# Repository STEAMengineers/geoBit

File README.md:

# geoBit
A GPS device for route tracking, GPS art or logging for OSM

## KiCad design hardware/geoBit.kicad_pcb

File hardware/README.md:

# Hardware

### Controller
[RP2354a](https://www.lcsc.com/product-detail/C41378174.html)

### Battery charger
[Injoinic IP5306-I2C](https://www.lcsc.com/product-detail/C488349.html)
Provides 2.1A boosted output at 5V. Use I2C to set registers to prevent the chip from entering sleep mode and read battery charge status. 

[Details of register settings](https://github.com/AvinasheeTech/IP5306_I2C)

### SD card
Uses SDIO (Four line) interface. The interface is protected with an [ST EMIF06-MSD02N16](https://www.lcsc.com/product-detail/C5267594.html?s_z=n_C5267594) chip

### GPS
[ATGM336H-6N-74](https://www.lcsc.com/product-detail/C5804601.html)

### Screen
[Good display GDEY0154D67](https://www.good-display.com/product/388.html)

### GPIO

| Pin  | Name  | Function  | Notes |
|---|---|---|---|
| GPIO_0  | CHGR_SDA  | 	I2C0 SDA  | |
| GPIO_1 | CHGR_SCL  | 	I2C0 SCL  | |
| GPIO_2 | CHGR_IRQ  | 	SIO  | |
| GPIO_3 | BUTTON1  | 	SIO  | |
| GPIO_4 | BUTTON2 | 	SIO  | |
| GPIO_5 | FILTERED_SD_CLK  | 	SIO  | |
| GPIO_6 | FILTERED_SD_CMD  | 	SIO  | |
| GPIO_7 | FILTERED_SD_DAT0  | 	SIO  | |
| GPIO_8 | FILTERED_SD_DAT1  | 	SIO  | |
| GPIO_9 | FILTERED_SD_DAT2  | 	SIO  | |
| GPIO_10 | FILTERED_SD_DAT3  | 	SIO  | |
| GPIO_11 | FILTERED_SD_DET  | 	SIO  | |
| GPIO_12 | GPS_RX  | 	UART0_TX  | |
| GPIO_13 | GPS_TX  | 	UART0_RX  | |
| GPIO_14 | GPS_1PPS  | 	SIO  | |
| GPIO_15 | STATUS_LED  | 	SIO  | |
| GPIO_16 | BUTTON3  | 	SIO  | |
| GPIO_17 | EINK_CS  | 	SPI1_CSn  | |
| GPIO_18 | EINK_SCLK  | 	SPI1_SCK  | |
| GPIO_19 | EINK_SDI  | 	SPI1_TX  | |
| GPIO_20 | EINK_D/C  | 	SIO  | |
| GPIO_21 | EINK_RES  | 	SIO  | |
| GPIO_22 | EINK_BUSY  | 	SIO  | |
| GPIO_23 | UNALLOCATED  | 	SIO  | |
| GPIO_24 | UNALLOCATED  | 	SIO  | |
| GPIO_25 | UNALLOCATED  | 	SIO  | |
| GPIO_26 | UNALLOCATED  | 	SIO  | ADC |
| GPIO_27 | UNALLOCATED  | 	SIO  | ADC |
| GPIO_28 | UNALLOCATED  | 	SIO  | ADC |
| GPIO_29 | UNALLOCATED  | 	SIO  | ADC |

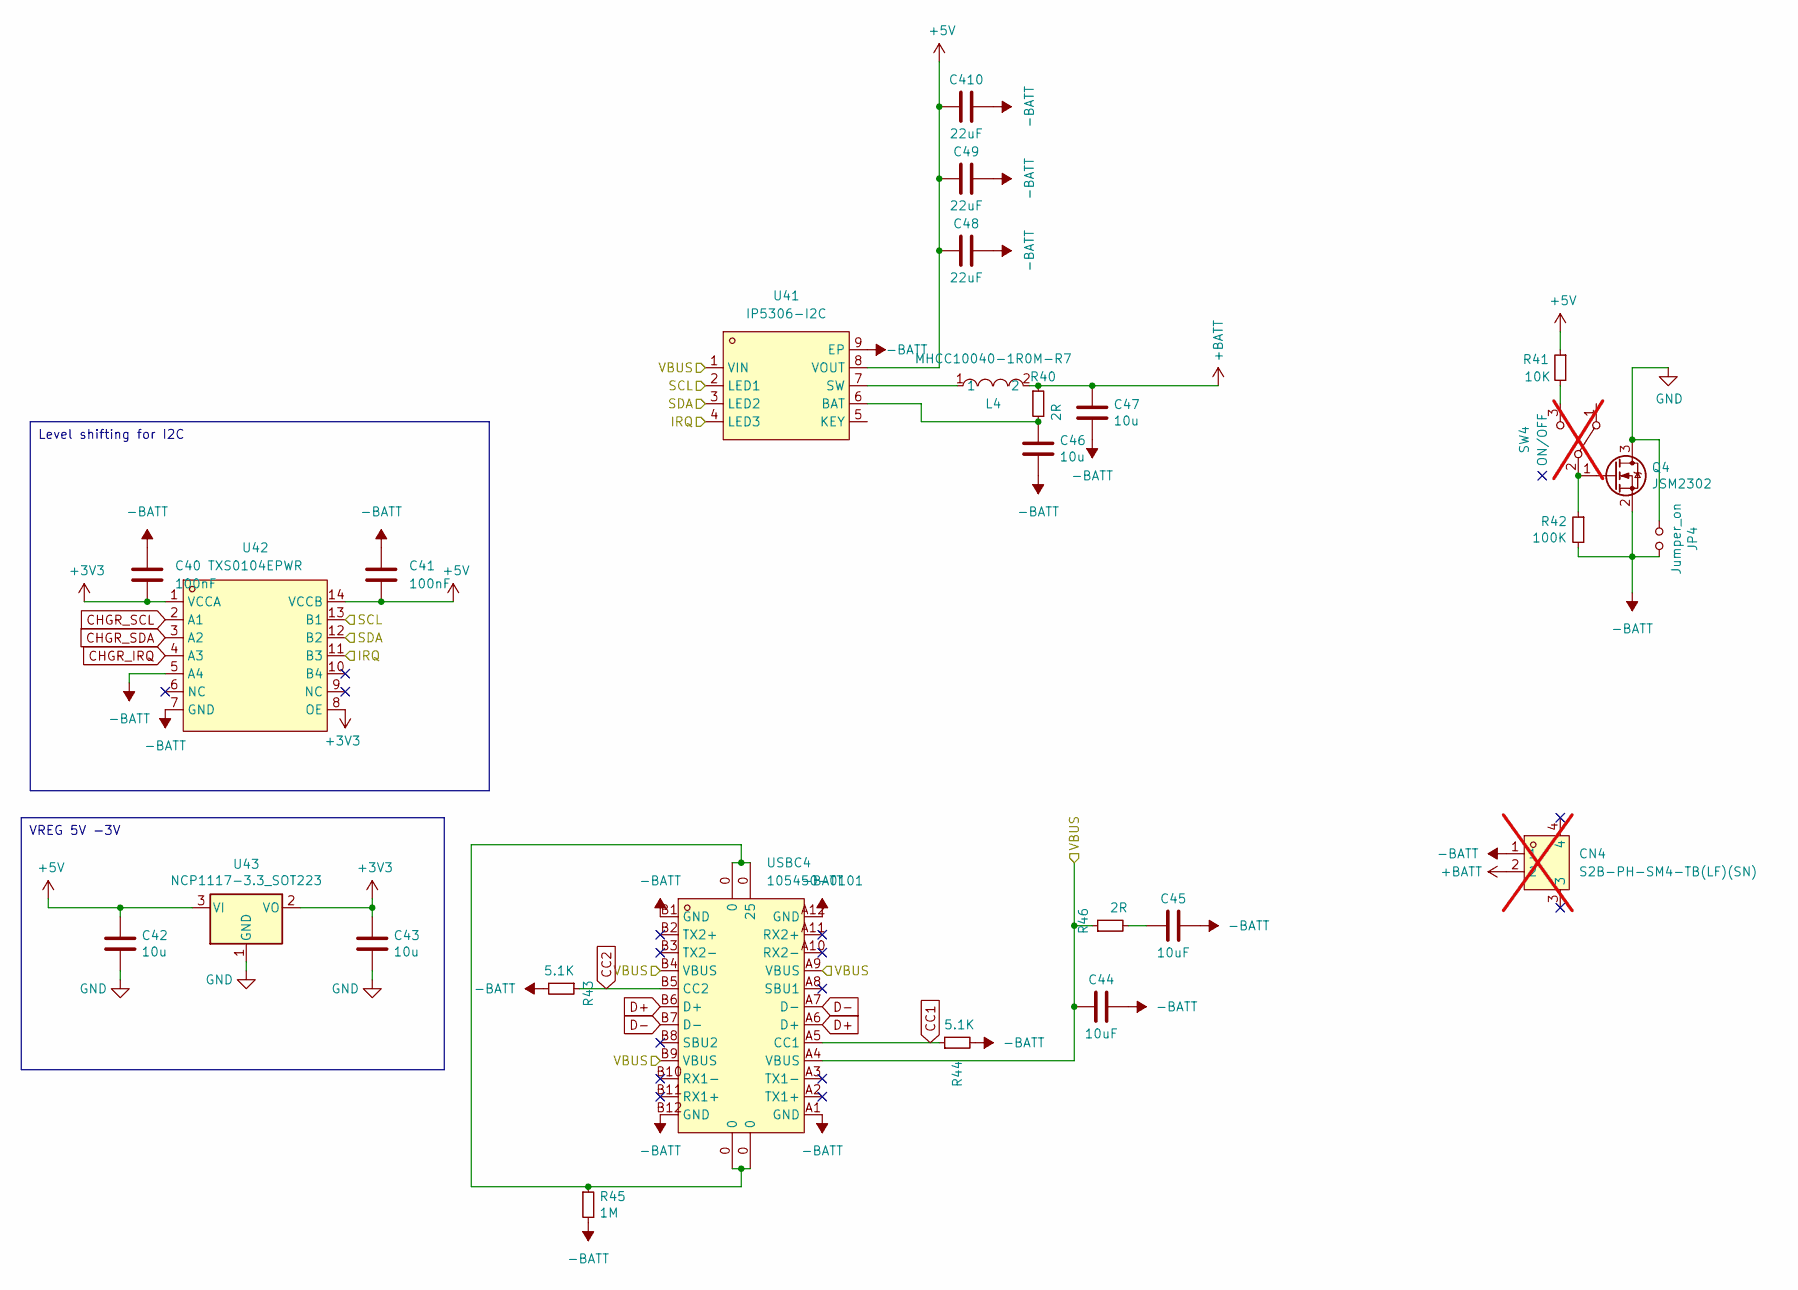
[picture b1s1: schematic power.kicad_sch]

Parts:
C40, C41: 100nF; C_0402_1005Metric_Pad0.74x0.62mm_HandSolder; LCSC C1525
C42, C43, C46, C47: 10u; C_0805_2012Metric
C44, C45: 10uF; C_0603_1608Metric_Pad1.08x0.95mm_HandSolder; LCSC C76614
C48, C49, C410: 22uF; C_0402_1005Metric_Pad0.74x0.62mm_HandSolder; LCSC C2179118
CN4: S2B-PH-SM4-TB(LF)(SN); CONN-SMD_P2.00_S2B-PH-SM4-TB-LF-SN; LCSC Part C295747; not fitted
JP4: Jumper_on; SolderJumper-2_P1.3mm_Open_RoundedPad1.0x1.5mm
L4: MHCC10040-1R0M-R7; IND-SMD_L11.6-W10.1; LCSC Part C280565
Q4: JSM2302; SOT-23; LCSC C916403
R40, R46: 2R; R_0402_1005Metric; Farnell 2447404
R41: 10K; R_0402_1005Metric; Farnell 2331740
R42: 100K; R_0402_1005Metric; Farnell 2073355
R43, R44: 5.1K; R_0402_1005Metric_Pad0.72x0.64mm_HandSolder; Farnell 2447404
R45: 1M; R_0402_1005Metric_Pad0.72x0.64mm_HandSolder; LCSC C26083
SW4: ON/OFF; SW_Slide_SPDT_Angled_CK_OS102011MA1Q; Farnell 1201431; not fitted
U41: IP5306-I2C; ESOP-8_L4.9-W3.9-P1.27-LS6.0-BL-EP2.0; LCSC Part C488349
U42: TXS0104EPWR; TSSOP-14_L5.0-W4.4-P0.65-LS6.4-BL; LCSC Part C44955
U43: NCP1117-3.3_SOT223; SOT-223-3_TabPin2; LCSC C26537
USBC4: 105450-0101; USB-C-SMD_TYPE-C-USB-18; LCSC C134092

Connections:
+3V3: C40.2, C43.1, U42.1 (VCCA), U42.8 (OE), U43.2 (VO); also elsewhere on the board
+5V: C41.2, C42.1, C48.1, C49.1, C410.1, R41.1, U41.8 (VOUT), U42.14 (VCCB), U43.3 (VI)
+BATT: C47.1, CN4.2, L4.2, R40.1
-BATT: C40.1, C41.1, C44.2, C45.2, C46.2, C47.2, C48.2, C49.2, C410.2, CN4.1, JP4.1, Q4.2 (S), R42.2, R43.2, R44.2, R45.2, U41.9 (EP), U42.5 (A4), U42.7 (GND), USBC4.A1 (GND), USBC4.A12 (GND), USBC4.B1 (GND), USBC4.B12 (GND); also elsewhere on the board
/power/IRQ: U41.4 (LED3), U42.11 (B3)
/power/SCL: U41.2 (LED1), U42.13 (B1)
/power/SDA: U41.3 (LED2), U42.12 (B2)
/power/VBUS: C44.1, R46.1, U41.1 (VIN), USBC4.A4 (VBUS), USBC4.A9 (VBUS), USBC4.B4 (VBUS), USBC4.B9 (VBUS); also elsewhere on the board
CHGR_IRQ: U42.4 (A3); also elsewhere on the board
CHGR_SCL: U42.2 (A1); also elsewhere on the board
CHGR_SDA: U42.3 (A2); also elsewhere on the board
GND: C42.2, C43.2, JP4.2, Q4.3 (D), U43.1 (GND); also elsewhere on the board
unnamed: C45.1, R46.2
unnamed: Q4.1 (G), R42.1, SW4.2 (B)
unnamed: R45.1, USBC4.0
unnamed: R41.2, SW4.3 (C)
unnamed: C46.1, R40.2, U41.6 (BAT)
unnamed: L4.1, U41.7 (SW)
unnamed 73: R44.1, USBC4.A5 (CC1); also elsewhere on the board
unnamed 74: R43.1, USBC4.B5 (CC2); also elsewhere on the board
unnamed: USBC4.A6 (D+), USBC4.B6 (D+)
unnamed: USBC4.A7 (D-), USBC4.B7 (D-)

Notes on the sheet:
Level shifting for I2C
VREG 5V -3V

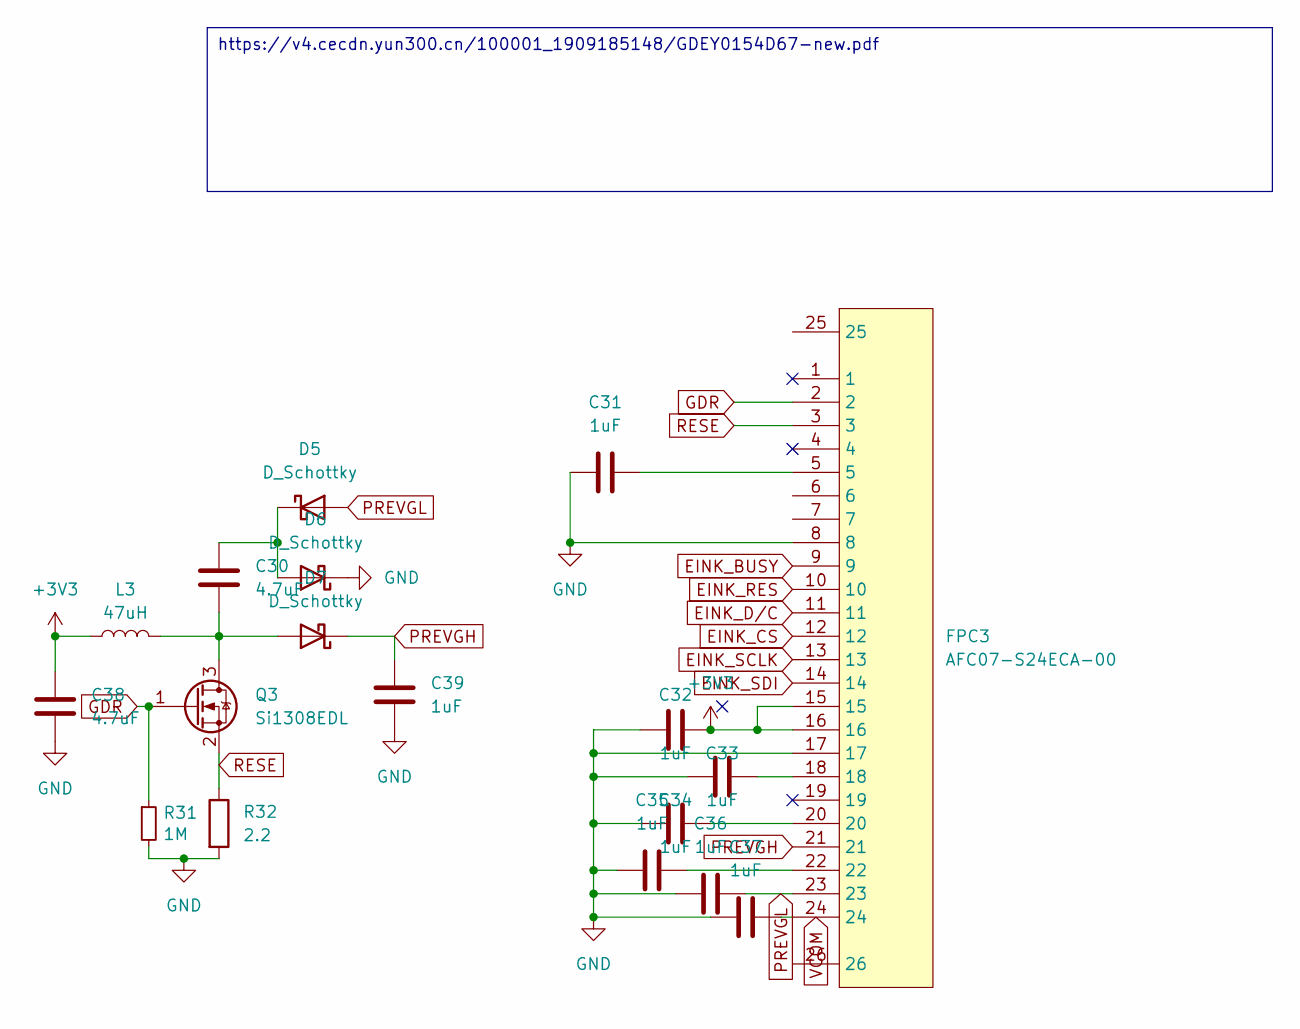
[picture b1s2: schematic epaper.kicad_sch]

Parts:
C30, C38: 4.7uF; C_0402_1005Metric; lcsc C6119795
C31, C32, C33, C34, C35, C36, C37, C39: 1uF; C_0402_1005Metric; lcsc C52923
D5, D6, D7: D_Schottky; D_SOD-323; lcsc C21714236
FPC3: AFC07-S24ECA-00; FPC-SMD_AFC07-S24ECA-00; LCSC Part C262643
L3: 47uH; L_0805_2012Metric; lcsc C19188767
Q3: Si1308EDL; SOT-323_SC-70; lcsc C7603347
R31: 1M; R_0402_1005Metric; LCSC C26083
R32: 2.2; R_0402_1005Metric; lcsc C327251

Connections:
+3V3: C32.1, C38.1, FPC3.15, FPC3.16, L3.1; also elsewhere on the board
EINK_BUSY: FPC3.9; also elsewhere on the board
EINK_CS: FPC3.12; also elsewhere on the board
EINK_D/C: FPC3.11; also elsewhere on the board
EINK_RES: FPC3.10; also elsewhere on the board
EINK_SCLK: FPC3.13; also elsewhere on the board
EINK_SDI: FPC3.14; also elsewhere on the board
GDR: FPC3.2, Q3.1 (G), R31.1
GND: C31.2, C32.2, C33.2, C34.2, C35.2, C36.2, C37.2, C38.2, C39.1, D6.1 (K), FPC3.8, FPC3.17, R31.2, R32.2; also elsewhere on the board
unnamed: C31.1, FPC3.5
unnamed: C33.1, FPC3.18
unnamed: C34.1, FPC3.20
unnamed: C35.1, FPC3.22
unnamed: C37.1, FPC3.24
unnamed: C30.1, D5.1 (K), D6.2 (A)
unnamed: C30.2, D7.2 (A), L3.2, Q3.3 (D)
PREVGH: C39.2, D7.1 (K), FPC3.21
PREVGL: C36.1, D5.2 (A), FPC3.23
RESE: FPC3.3, Q3.2 (S), R32.1

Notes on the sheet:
https://v4.cecdn.yun300.cn/100001_1909185148/GDEY0154D67-new.pdf

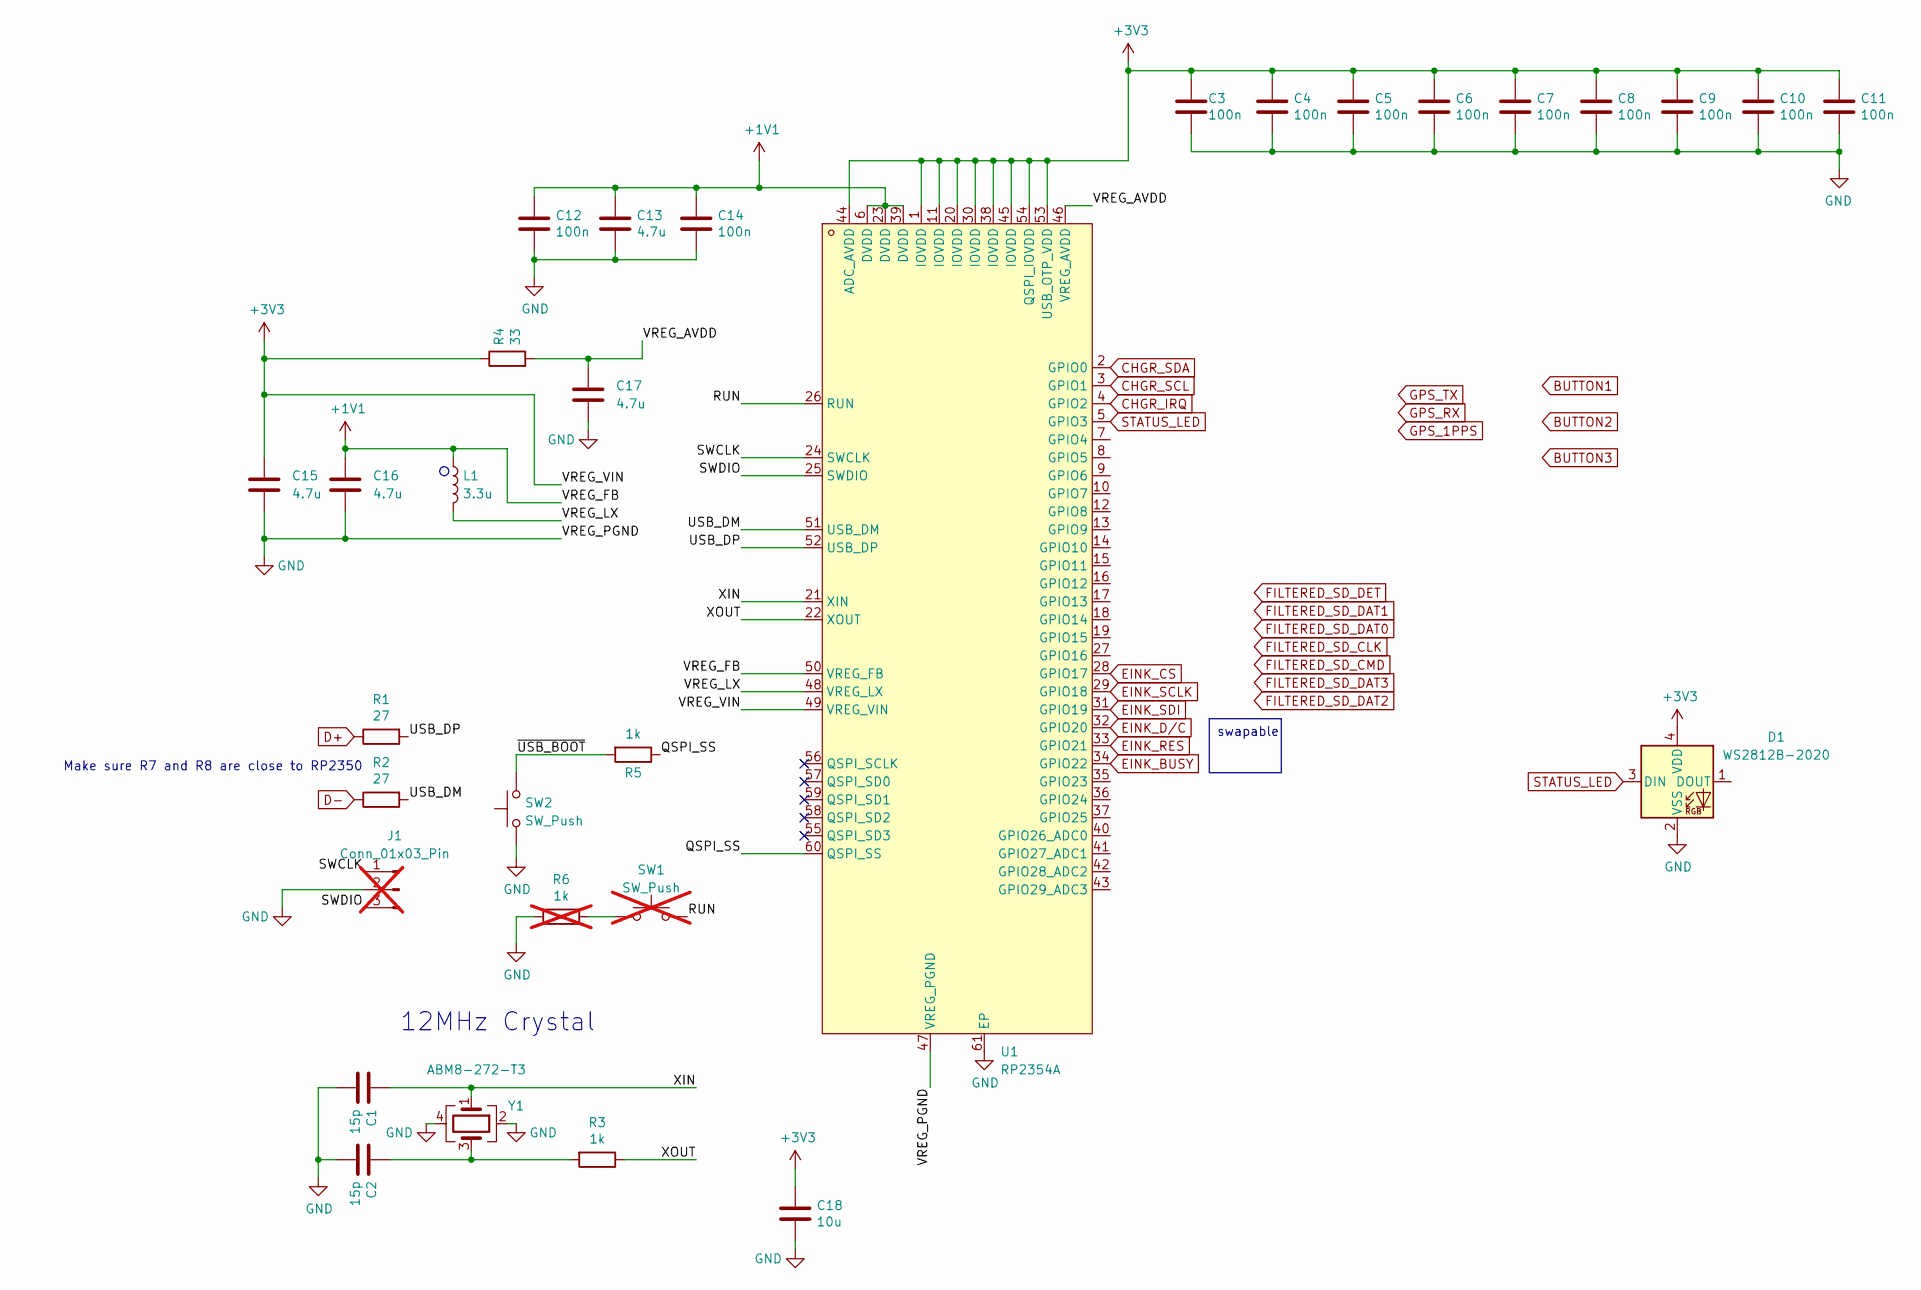
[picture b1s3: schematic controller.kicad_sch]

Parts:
C1, C2: 15p; C_0402_1005Metric; LCSC C326803
C3, C4, C5, C6, C7, C8, C9, C10, C11, C12, C14: 100n; C_0402_1005Metric; LCSC C77020
C13: 4.7u; C_0402_1005Metric
C15, C16: 4.7u; C_0603_1608Metric; LCSC C1705
C17: 4.7u; C_0402_1005Metric; LCSC C23733
C18: 10u; C_0805_2012Metric
D1: WS2812B-2020; LED_WS2812B-2020_PLCC4_2.0x2.0mm
J1: Conn_01x03_Pin; PinHeader_1x03_P2.54mm_Vertical; not fitted
L1: 3.3u; IND-SMD_L2.0-W1.6_AOTA-B201610S3R3-101-T; LCSC C42411119
R1, R2: 27; R_0402_1005Metric; LCSC C138021
R3, R5: 1k; R_0402_1005Metric; LCSC C106235
R4: 33; R_0402_1005Metric; LCSC C138002
R6: 1k; R_0402_1005Metric; LCSC C106235; not fitted
SW1: SW_Push; SW-SMD_L3.9-W3.0-P4.45; LCSC C720477; not fitted
SW2: SW_Push; SW-SMD_L3.9-W3.0-P4.45; LCSC C720477
U1: RP2354A; QFN-60_L7.0-W7.0-P0.40-TL-EP3.4; LCSC Part C41378174
Y1: ABM8-272-T3; Crystal_SMD_3225-4Pin_3.2x2.5mm; LCSC C20625731

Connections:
+1V1: C12.1, C13.1, C14.1, C16.1, L1.1, U1.6 (DVDD), U1.23 (DVDD), U1.39 (DVDD), U1.50 (VREG_FB)
+3V3: C3.1, C4.1, C5.1, C6.1, C7.1, C8.1, C9.1, C10.1, C11.1, C15.1, C18.1, D1.4 (VDD), J1.5, R4.1, U1.1 (IOVDD), U1.11 (IOVDD), U1.20 (IOVDD), U1.30 (IOVDD), U1.38 (IOVDD), U1.44 (ADC_AVDD), U1.45 (IOVDD), U1.49 (VREG_VIN), U1.53 (USB_OTP_VDD), U1.54 (QSPI_IOVDD); also elsewhere on the board
/controller/QSPI_SS: R5.1, U1.60 (QSPI_SS)
/controller/RUN: SW1.2, U1.26 (RUN)
/controller/SWCLK: J1.1, U1.24 (SWCLK)
/controller/SWDIO: J1.3, U1.25 (SWDIO)
/controller/USB_DM: R2.2, U1.51 (USB_DM)
/controller/USB_DP: R1.2, U1.52 (USB_DP)
/controller/VREG_AVDD: C17.1, R4.2, U1.46 (VREG_AVDD)
/controller/VREG_LX: L1.2, U1.48 (VREG_LX)
/controller/XIN: C1.1, U1.21 (XIN), Y1.1
/controller/XOUT: R3.1, U1.22 (XOUT)
/controller/~USB_BOOT: R5.2, SW2.2
BUTTON2: U1.7 (GPIO4); also elsewhere on the board
BUTTON3: U1.27 (GPIO16); also elsewhere on the board
CHGR_IRQ: U1.4 (GPIO2); also elsewhere on the board
CHGR_SCL: U1.3 (GPIO1); also elsewhere on the board
CHGR_SDA: U1.2 (GPIO0); also elsewhere on the board
D+: R1.1; also elsewhere on the board
D-: R2.1; also elsewhere on the board
EINK_BUSY: U1.34 (GPIO22); also elsewhere on the board
EINK_CS: U1.28 (GPIO17); also elsewhere on the board
EINK_D/C: U1.32 (GPIO20); also elsewhere on the board
EINK_RES: U1.33 (GPIO21); also elsewhere on the board
EINK_SCLK: U1.29 (GPIO18); also elsewhere on the board
EINK_SDI: U1.31 (GPIO19); also elsewhere on the board
FILTERED_SD_CLK: U1.8 (GPIO5); also elsewhere on the board
FILTERED_SD_CMD: U1.9 (GPIO6); also elsewhere on the board
FILTERED_SD_DAT0: U1.10 (GPIO7); also elsewhere on the board
FILTERED_SD_DAT1: U1.12 (GPIO8); also elsewhere on the board
FILTERED_SD_DAT2: U1.13 (GPIO9); also elsewhere on the board
FILTERED_SD_DAT3: U1.14 (GPIO10); also elsewhere on the board
GND: C1.2, C2.2, C3.2, C4.2, C5.2, C6.2, C7.2, C8.2, C9.2, C10.2, C11.2, C12.2, C13.2, C14.2, C15.2, C16.2, C17.2, C18.2, D1.2 (VSS), J1.2, J1.4, R6.2, SW2.1, U1.47 (VREG_PGND), U1.61 (EP), Y1.2, Y1.4; also elsewhere on the board
GPIO23: J1.6, U1.35 (GPIO23)
GPIO24: J1.7, U1.36 (GPIO24)
GPIO25: J1.8, U1.37 (GPIO25)
GPIO26_ADC0: J1.9, U1.40 (GPIO26_ADC0)
GPIO27_ADC1: J1.10, U1.41 (GPIO27_ADC1)
GPIO28_ADC2: J1.11, U1.42 (GPIO28_ADC2)
GPIO29_ADC3: J1.12, U1.43 (GPIO29_ADC3)
GPS_1PPS: U1.18 (GPIO14); also elsewhere on the board
GPS_RX: U1.16 (GPIO12); also elsewhere on the board
GPS_TX: U1.17 (GPIO13); also elsewhere on the board
unnamed: C2.1, R3.2, Y1.3
unnamed: R6.1, SW1.1
SD_DET: U1.15 (GPIO11); also elsewhere on the board

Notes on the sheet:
swapable
Make sure R7 and R8 are close to RP2350
12MHz Crystal

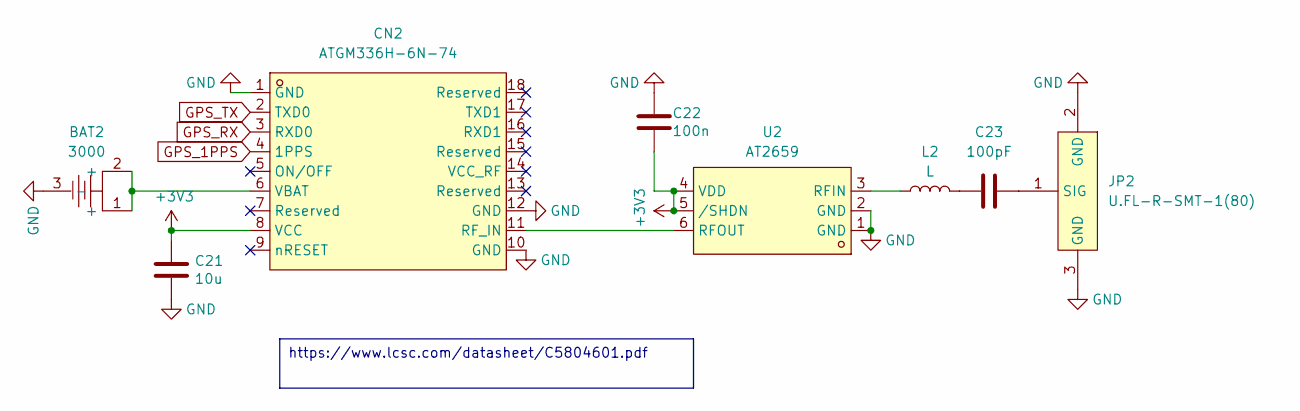
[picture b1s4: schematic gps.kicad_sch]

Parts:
BAT2: 3000; BAT-SMD_CR1202; LCSC Part C238097
C21: 10u; C_0805_2012Metric
C22: 100n; C_0402_1005Metric; LCSC C77020
C23: 100pF; C_0402_1005Metric_Pad0.74x0.62mm_HandSolder; lcsc C106200
CN2: ATGM336H-6N-74; ATGM336H-5N31; LCSC Part C5804601
JP2: U.FL-R-SMT-1(80); RF-SMD_FRF05002-JSS103M; LCSC Part C88374
L2: L; L_0402_1005Metric; lcsc C77110
U2: AT2659; DFN-6_L1.6-W1.0-P0.55-BL; LCSC Part C92450

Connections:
+3V3: C21.1, C22.2, CN2.8 (VCC), U2.4 (VDD), U2.5 (/SHDN); also elsewhere on the board
GND: BAT2.3 (-), C21.2, C22.1, CN2.1 (GND), CN2.10 (GND), CN2.12 (GND), JP2.2 (GND), JP2.3 (GND), U2.1 (GND), U2.2 (GND); also elsewhere on the board
GPS_1PPS: CN2.4 (1PPS); also elsewhere on the board
GPS_RX: CN2.3 (RXD0); also elsewhere on the board
GPS_TX: CN2.2 (TXD0); also elsewhere on the board
unnamed: C23.1, L2.2
unnamed: CN2.11 (RF_IN), U2.6 (RFOUT)
unnamed: BAT2.1 (+), BAT2.2 (+), CN2.6 (VBAT)
unnamed: C23.2, JP2.1 (SIG)
unnamed: L2.1, U2.3 (RFIN)

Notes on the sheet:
https://www.lcsc.com/datasheet/C5804601.pdf

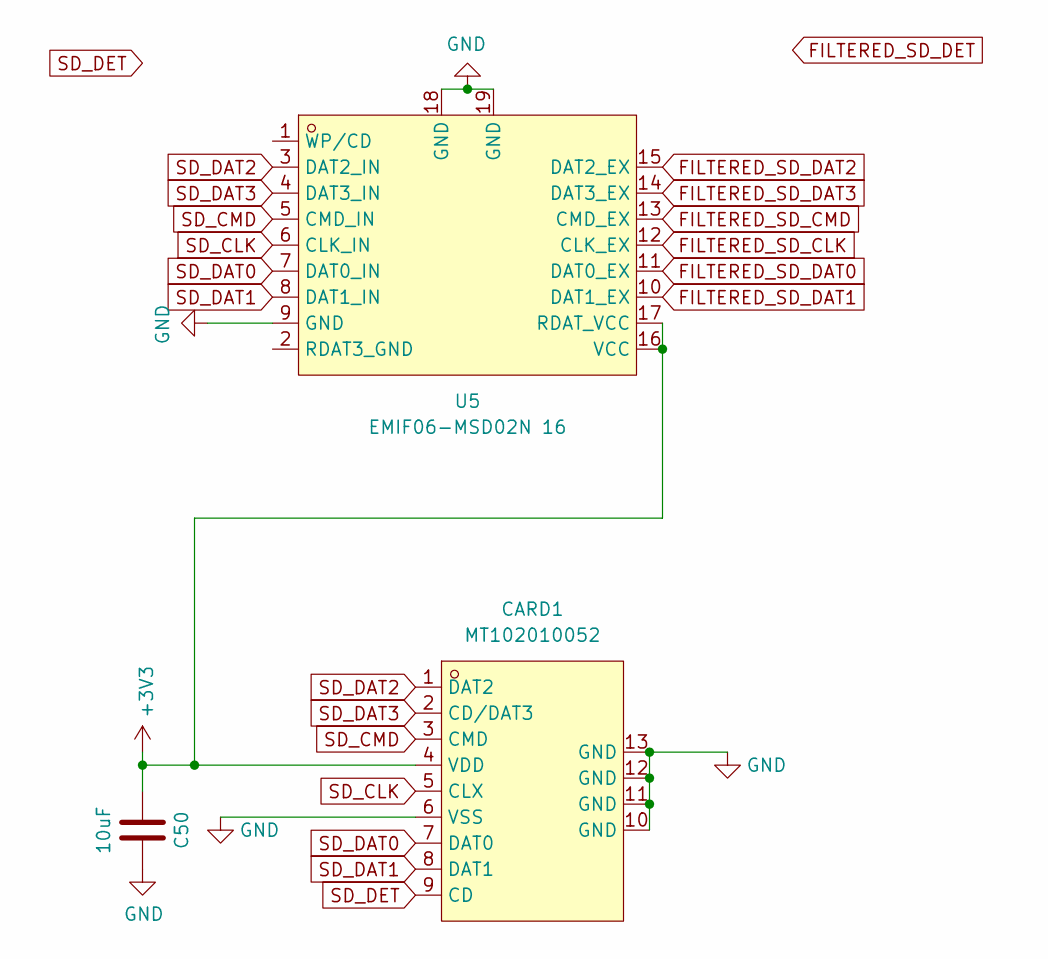
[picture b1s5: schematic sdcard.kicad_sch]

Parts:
C50: 10uF; C_0603_1608Metric_Pad1.08x0.95mm_HandSolder; LCSC C76614
CARD1: MT102010052; TF-CARD-SMD_MT102010052; LCSC Part C7462320
U5: EMIF06-MSD02N 16; QFN-16L_L3.5-W1.2-P0.40_EMIF06-MSD02N16; LCSC Part C5267594

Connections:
+3V3: C50.1, CARD1.4 (VDD), U5.16 (VCC), U5.17 (RDAT_VCC); also elsewhere on the board
FILTERED_SD_CLK: CARD1.5 (CLX), U5.6 (CLK_IN); also elsewhere on the board
FILTERED_SD_CMD: CARD1.3 (CMD), U5.5 (CMD_IN); also elsewhere on the board
FILTERED_SD_DAT0: CARD1.7 (DAT0), U5.7 (DAT0_IN); also elsewhere on the board
FILTERED_SD_DAT1: CARD1.8 (DAT1), U5.8 (DAT1_IN); also elsewhere on the board
FILTERED_SD_DAT2: CARD1.1 (DAT2), U5.3 (DAT2_IN); also elsewhere on the board
FILTERED_SD_DAT3: CARD1.2 (CD/DAT3), U5.4 (DAT3_IN); also elsewhere on the board
GND: C50.2, CARD1.6 (VSS), CARD1.10 (GND), CARD1.11 (GND), CARD1.12 (GND), CARD1.13 (GND), U5.9 (GND), U5.18 (GND), U5.19 (GND); also elsewhere on the board
SD_CLK: U5.12 (CLK_EX); also elsewhere on the board
SD_CMD: U5.13 (CMD_EX); also elsewhere on the board
SD_DAT0: U5.11 (DAT0_EX); also elsewhere on the board
SD_DAT1: U5.10 (DAT1_EX); also elsewhere on the board
SD_DAT2: U5.15 (DAT2_EX); also elsewhere on the board
SD_DAT3: U5.14 (DAT3_EX); also elsewhere on the board
SD_DET: U5.1 (WP/CD); also elsewhere on the board

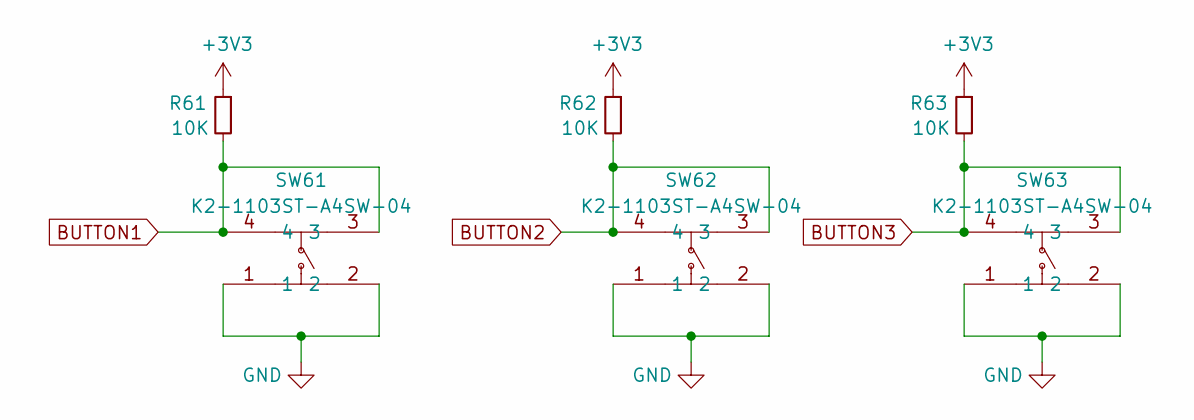
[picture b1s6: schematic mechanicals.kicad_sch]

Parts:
R61, R62, R63: 10K; R_0402_1005Metric; Farnell 2331740
SW61, SW62, SW63: K2-1103ST-A4SW-04; KEY-SMD_4P-L12.0-W12.0-P5.00-LS15.1; LCSC Part C879472

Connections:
+3V3: R61.1, R62.1, R63.1; also elsewhere on the board
BUTTON2: R62.2, SW62.3, SW62.4; also elsewhere on the board
BUTTON3: R63.2, SW63.3, SW63.4; also elsewhere on the board
GND: SW61.1, SW61.2, SW62.1, SW62.2, SW63.1, SW63.2; also elsewhere on the board

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
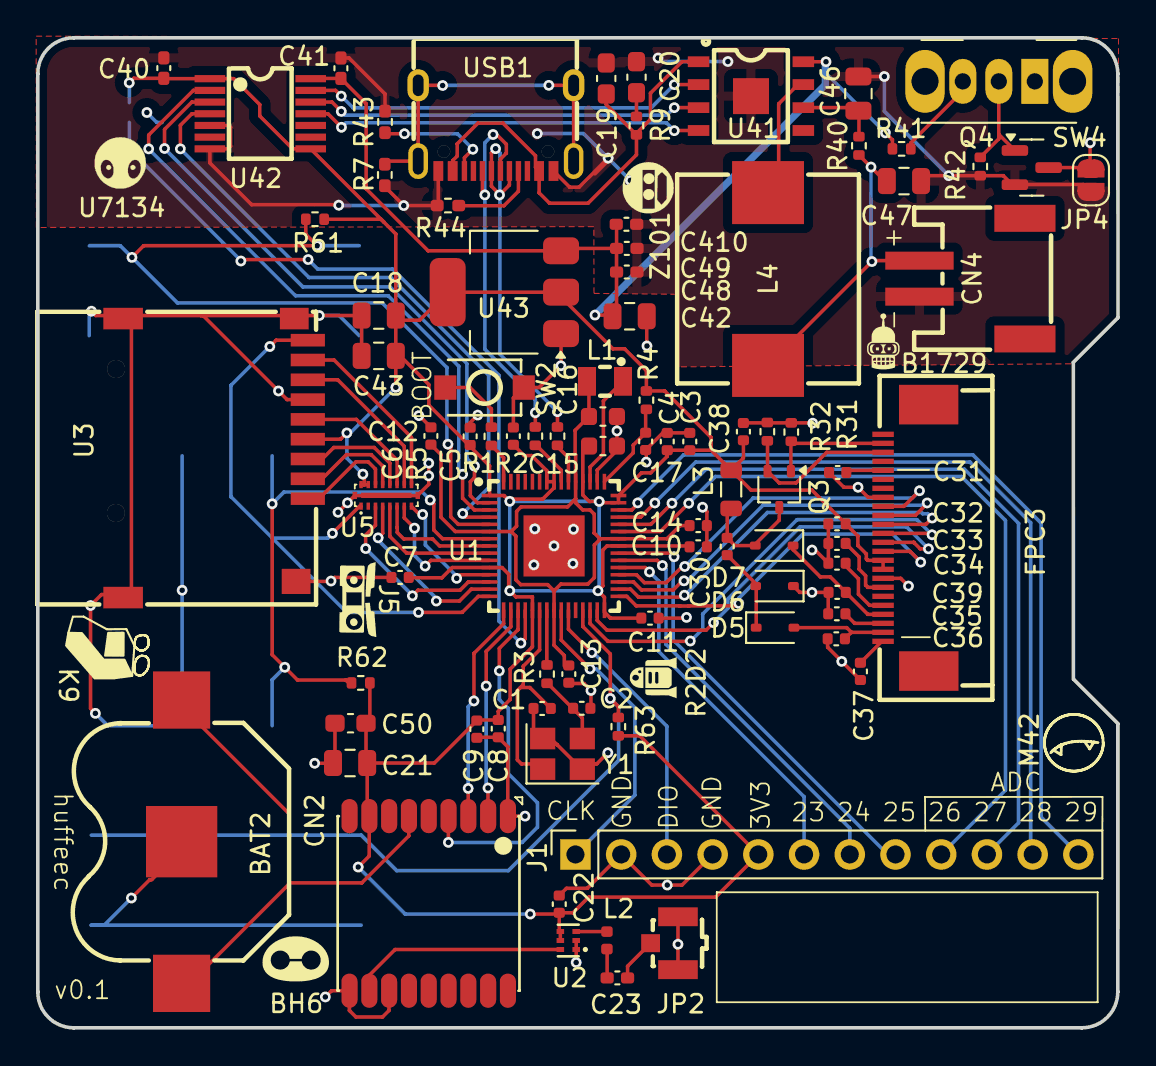
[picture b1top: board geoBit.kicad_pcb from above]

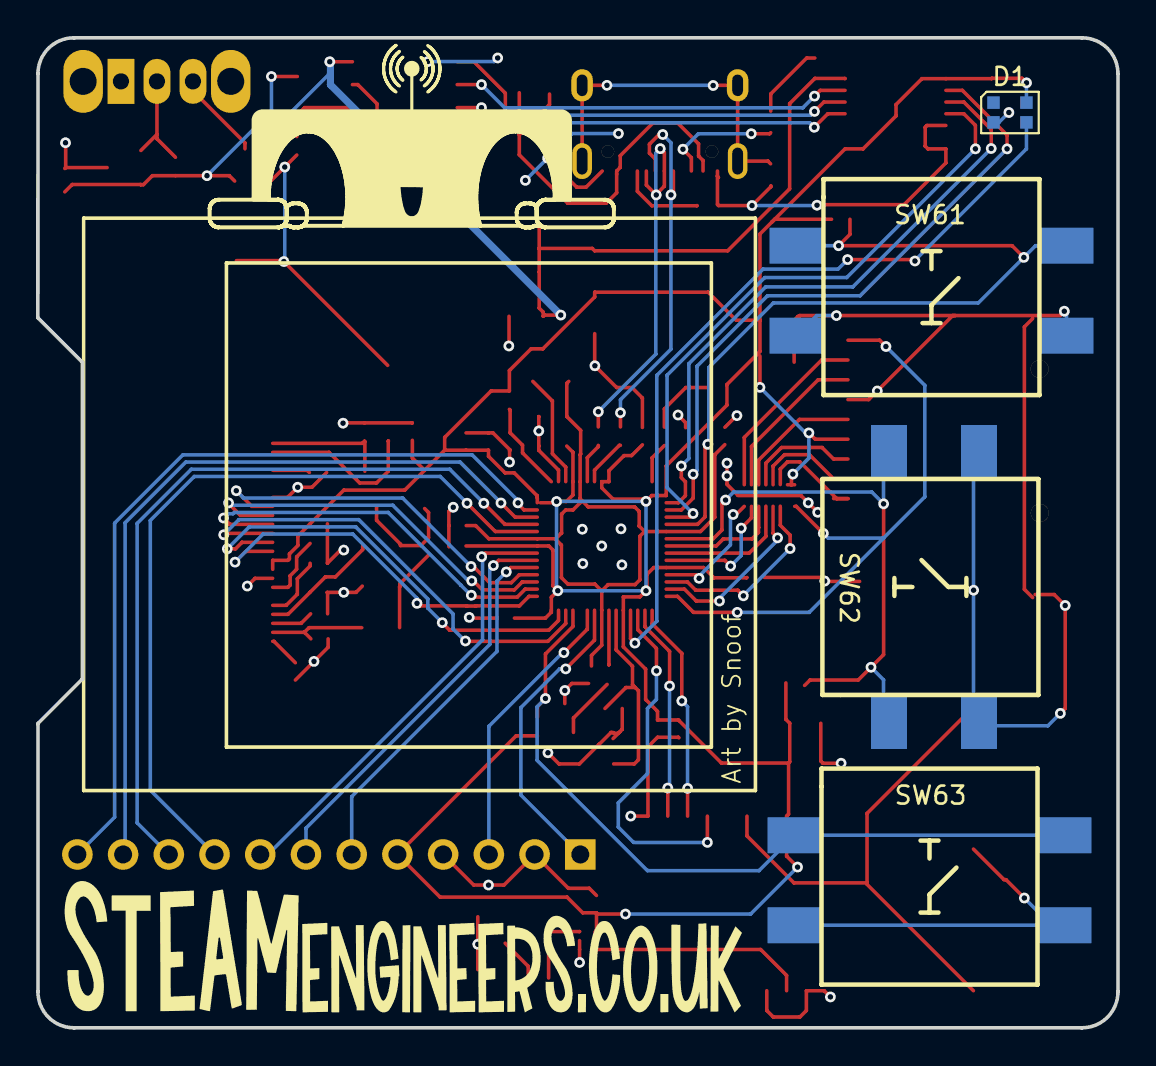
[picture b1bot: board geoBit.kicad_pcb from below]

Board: 4 copper layers, 60.0 x 55.0 mm, 91 parts (4 on the bottom side), 83 nets.

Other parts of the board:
C19, C20: 10uF; C_0603_1608Metric_Pad1.08x0.95mm_HandSolder
R7: 1M; R_0402_1005Metric_Pad0.72x0.64mm_HandSolder
R9: 2R; R_0402_1005Metric
U3: MR01A-01239; TF-SMD_MR01A-01211
USB1: TYPE-C 16PIN 2MD(073); USB-C-SMD_TYPE-C-6PIN-2MD-073

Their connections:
+3V3: U3.4 (VDD); also elsewhere on the board
-BATT: C19.2, C20.2, R7.2, USB1.1 (GND), USB1.12 (GND); also elsewhere on the board
/power/VBUS: C19.1, R9.1, USB1.2 (VBUS), USB1.11 (VBUS); also elsewhere on the board
D+: USB1.6 (DP1), USB1.8 (DP2); also elsewhere on the board
D-: USB1.5 (DN2), USB1.7 (DN1); also elsewhere on the board
GND: U3.6 (VSS), U3.10, U3.11, U3.12, U3.13; also elsewhere on the board
unnamed: C20.1, R9.2
unnamed: R7.1, USB1.13 (SHELL), USB1.14 (SHELL)
unnamed 73: USB1.4 (CC1); also elsewhere on the board
unnamed 74: USB1.10 (CC2); also elsewhere on the board
SD_CLK: U3.5 (CLK); also elsewhere on the board
SD_CMD: U3.3 (CMD); also elsewhere on the board
SD_DAT0: U3.7 (DAT0); also elsewhere on the board
SD_DAT1: U3.8 (DAT1); also elsewhere on the board
SD_DAT2: U3.1 (DAT2); also elsewhere on the board
SD_DAT3: U3.2 (CD/DAT3); also elsewhere on the board
SD_DET: U3.9; also elsewhere on the board

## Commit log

2026-03-01 Initial hardware commit
2026-03-01 Add initial hardware description to README
2026-03-02 Update README with GPIO pinout details
    Added detailed GPIO pinout information to the README.
2026-03-03 Document unallocated GPIO pins in README
    Added unallocated GPIO pins to the hardware README.
2026-03-03 Expand hardware README with component details
    Added detailed hardware components and specifications.
2026-04-04 Updated pcb v0.1
